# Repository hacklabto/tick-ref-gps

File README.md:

tick-ref-gps
============

GPS reference clock module for tick.hacklab.to. Part of tick-ref chassis.

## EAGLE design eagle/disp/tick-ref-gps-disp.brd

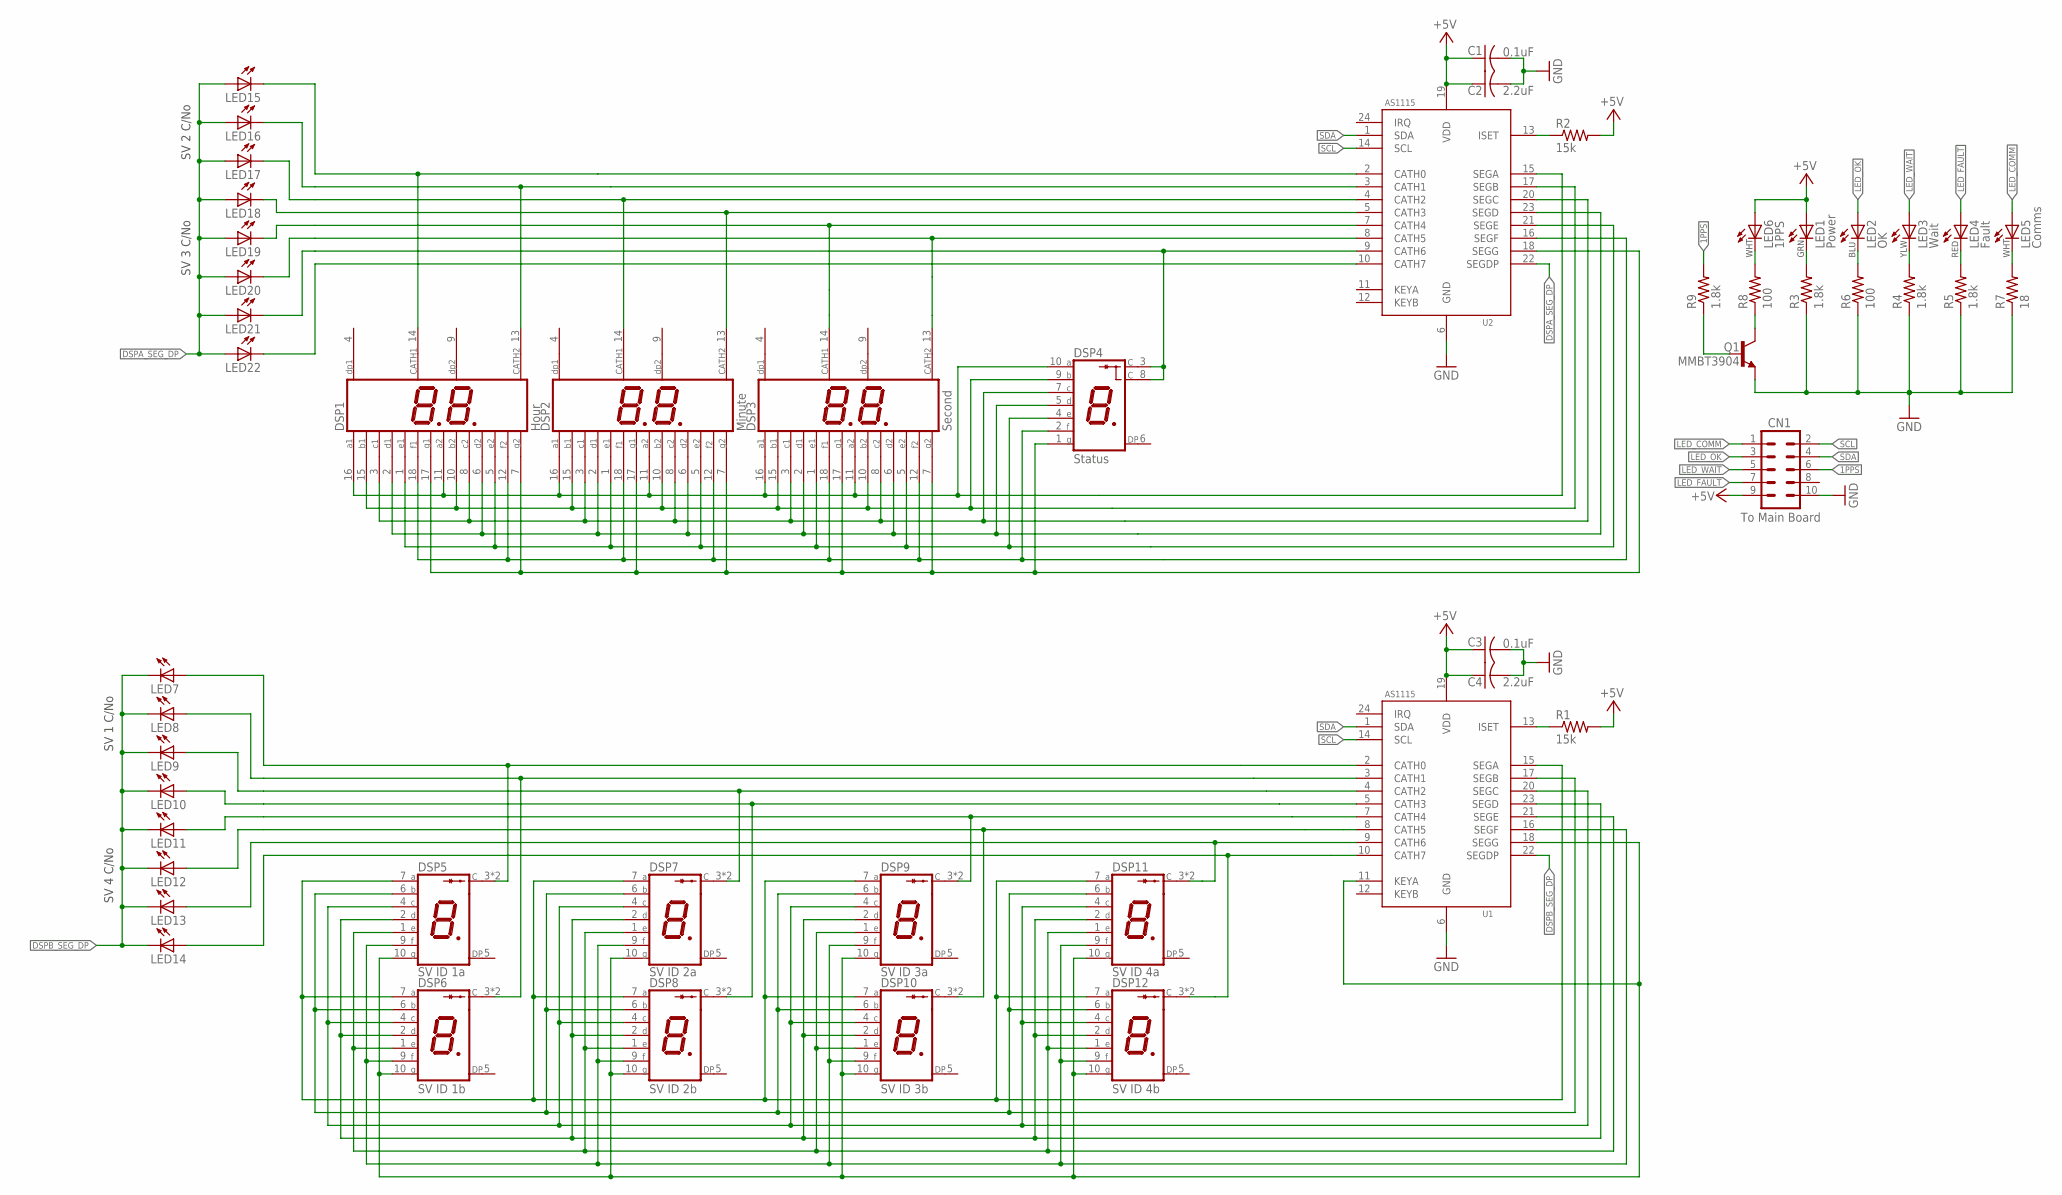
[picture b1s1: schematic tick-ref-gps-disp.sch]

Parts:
C1, C3: 0.1uF; C0603
C2, C4: 2.2uF; C0805
CN1: To Main Board; AVR_ICSP
DSP1: Hour; LUMEX-LDD-C81XRI
DSP2: Minute; LUMEX-LDD-C81XRI
DSP3: Second; LUMEX-LDD-C81XRI
DSP4: Status; S4301B
DSP5: SV ID 1a; KINGBRIGHT-ACSA02
DSP6: SV ID 1b; KINGBRIGHT-ACSA02
DSP7: SV ID 2a; KINGBRIGHT-ACSA02
DSP8: SV ID 2b; KINGBRIGHT-ACSA02
DSP9: SV ID 3a; KINGBRIGHT-ACSA02
DSP10: SV ID 3b; KINGBRIGHT-ACSA02
DSP11: SV ID 4a; KINGBRIGHT-ACSA02
DSP12: SV ID 4b; KINGBRIGHT-ACSA02
LED1: Power; LED5MM
LED2: OK; LED5MM
LED3: Wait; LED5MM
LED4: Fault; LED5MM
LED5: Comms; LED5MM
LED6: 1PPS; LED5MM
LED7, LED8, LED9, LED10, LED11, LED12, LED13, LED14, LED15, LED16, LED17, LED18, LED19, LED20, LED21, LED22: LEDCHIP-LED0805; CHIP-LED0805
Q1: MMBT3904; SOT23
R1, R2: 15k; R0603
R3, R4, R5, R9: 1.8k; R0603
R6, R8: 100; R0603
R7: 18; R0603
U1, U2: AS1115; QSOP24

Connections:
1PPS: CN1.6, R9.2
1PPS_Q: Q1.1 (B), R9.1
1PPS_R_Q: Q1.3 (C), R8.1
+5V: C1.1, C2.1, C3.1, C4.1, CN1.9, LED1.A, LED6.A, R1.2, R2.2, U1.19 (VDD), U2.19 (VDD)
CATH_HOUR_LS: DSP1.13 (CATH2), LED16.C, U2.3 (CATH1)
CATH_HOUR_MS: DSP1.14 (CATH1), LED15.C, U2.2 (CATH0)
CATH_MIN_LS: DSP2.13 (CATH2), LED18.C, U2.5 (CATH3)
CATH_MIN_MS: DSP2.14 (CATH1), LED17.C, U2.4 (CATH2)
CATH_SEC_LS: DSP3.13 (CATH2), LED20.C, U2.8 (CATH5)
CATH_SEC_MS: DSP3.14 (CATH1), LED19.C, U2.7 (CATH4)
CATH_STATUS_MS: DSP4.3 (C), DSP4.8 (C), LED21.C, U2.9 (CATH6)
CATH_STRENGTH: LED22.C, U2.10 (CATH7)
DSP5-C: DSP5.3 (CATH), DSP5.8 (CATH), LED7.A, U1.2 (CATH0)
DSP6-C: DSP6.3 (CATH), DSP6.8 (CATH), LED8.A, U1.3 (CATH1)
DSP7-C: DSP7.3 (CATH), DSP7.8 (CATH), LED9.A, U1.4 (CATH2)
DSP8-C: DSP8.3 (CATH), DSP8.8 (CATH), LED10.A, U1.5 (CATH3)
DSP9-C: DSP9.3 (CATH), DSP9.8 (CATH), LED11.A, U1.7 (CATH4)
DSP10-C: DSP10.3 (CATH), DSP10.8 (CATH), LED12.A, U1.8 (CATH5)
DSP11-C: DSP11.3 (CATH), DSP11.8 (CATH), LED13.A, U1.9 (CATH6)
DSP12-C: DSP12.3 (CATH), DSP12.8 (CATH), LED14.A, U1.10 (CATH7)
DSPA_SEG_A: DSP1.11 (A2), DSP1.16 (A1), DSP2.11 (A2), DSP2.16 (A1), DSP3.11 (A2), DSP3.16 (A1), DSP4.10 (A), U2.15 (SEGA)
DSPA_SEG_B: DSP1.10 (B2), DSP1.15 (B1), DSP2.10 (B2), DSP2.15 (B1), DSP3.10 (B2), DSP3.15 (B1), DSP4.9 (B), U2.17 (SEGB)
DSPA_SEG_C: DSP1.3 (C1), DSP1.8 (C2), DSP2.3 (C1), DSP2.8 (C2), DSP3.3 (C1), DSP3.8 (C2), DSP4.7 (C), U2.20 (SEGC)
DSPA_SEG_D: DSP1.2 (D1), DSP1.6 (D2), DSP2.2 (D1), DSP2.6 (D2), DSP3.2 (D1), DSP3.6 (D2), DSP4.5 (D), U2.23 (SEGD)
DSPA_SEG_DP: LED15.A, LED16.A, LED17.A, LED18.A, LED19.A, LED20.A, LED21.A, LED22.A, U2.22 (SEGDP)
DSPA_SEG_E: DSP1.1 (E1), DSP1.5 (E2), DSP2.1 (E1), DSP2.5 (E2), DSP3.1 (E1), DSP3.5 (E2), DSP4.4 (E), U2.21 (SEGE)
DSPA_SEG_F: DSP1.12 (F2), DSP1.18 (F1), DSP2.12 (F2), DSP2.18 (F1), DSP3.12 (F2), DSP3.18 (F1), DSP4.2 (F), U2.16 (SEGF)
DSPA_SEG_G: DSP1.7 (G2), DSP1.17 (G1), DSP2.7 (G2), DSP2.17 (G1), DSP3.7 (G2), DSP3.17 (G1), DSP4.1 (G), U2.18 (SEGG)
DSPB_SEG_A: DSP5.7 (A), DSP6.7 (A), DSP7.7 (A), DSP8.7 (A), DSP9.7 (A), DSP10.7 (A), DSP11.7 (A), DSP12.7 (A), U1.15 (SEGA)
DSPB_SEG_B: DSP5.6 (B), DSP6.6 (B), DSP7.6 (B), DSP8.6 (B), DSP9.6 (B), DSP10.6 (B), DSP11.6 (B), DSP12.6 (B), U1.17 (SEGB)
DSPB_SEG_C: DSP5.4 (C), DSP6.4 (C), DSP7.4 (C), DSP8.4 (C), DSP9.4 (C), DSP10.4 (C), DSP11.4 (C), DSP12.4 (C), U1.20 (SEGC)
DSPB_SEG_D: DSP5.2 (D), DSP6.2 (D), DSP7.2 (D), DSP8.2 (D), DSP9.2 (D), DSP10.2 (D), DSP11.2 (D), DSP12.2 (D), U1.23 (SEGD)
DSPB_SEG_DP: LED7.C, LED8.C, LED9.C, LED10.C, LED11.C, LED12.C, LED13.C, LED14.C, U1.22 (SEGDP)
DSPB_SEG_E: DSP5.1 (E), DSP6.1 (E), DSP7.1 (E), DSP8.1 (E), DSP9.1 (E), DSP10.1 (E), DSP11.1 (E), DSP12.1 (E), U1.21 (SEGE)
DSPB_SEG_F: DSP5.9 (F), DSP6.9 (F), DSP7.9 (F), DSP8.9 (F), DSP9.9 (F), DSP10.9 (F), DSP11.9 (F), DSP12.9 (F), U1.16 (SEGF)
DSPB_SEG_G: DSP5.10 (G), DSP6.10 (G), DSP7.10 (G), DSP8.10 (G), DSP9.10 (G), DSP10.10 (G), DSP11.10 (G), DSP12.10 (G), U1.11 (KEYA), U1.18 (SEGG)
GND: C1.2, C2.2, C3.2, C4.2, CN1.10, Q1.2 (E), R3.1, R4.1, R5.1, R6.1, R7.1, U1.6 (GND), U2.6 (GND)
LED1_R: LED1.K (C), R3.2
LED2_R: LED2.K (C), R6.2
LED3_R: LED3.K (C), R4.2
LED4_R: LED4.K (C), R5.2
LED5_R: LED5.K (C), R7.2
LED6_R: LED6.K (C), R8.2
LED_COMM: CN1.1, LED5.A
LED_FAULT: CN1.7, LED4.A
LED_ISET: R2.1, U2.13 (ISET)
LED_ISET1: R1.1, U1.13 (ISET)
LED_OK: CN1.3, LED2.A
LED_WAIT: CN1.5, LED3.A
SCL: CN1.2, U1.14 (SCL), U2.14 (SCL)
SDA: CN1.4, U1.1 (SDA), U2.1 (SDA)

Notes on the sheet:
GRN
YLW
RED
WHT
BLU
SV 1 C/No
SV 4 C/No
SV 2 C/No
SV 3 C/No

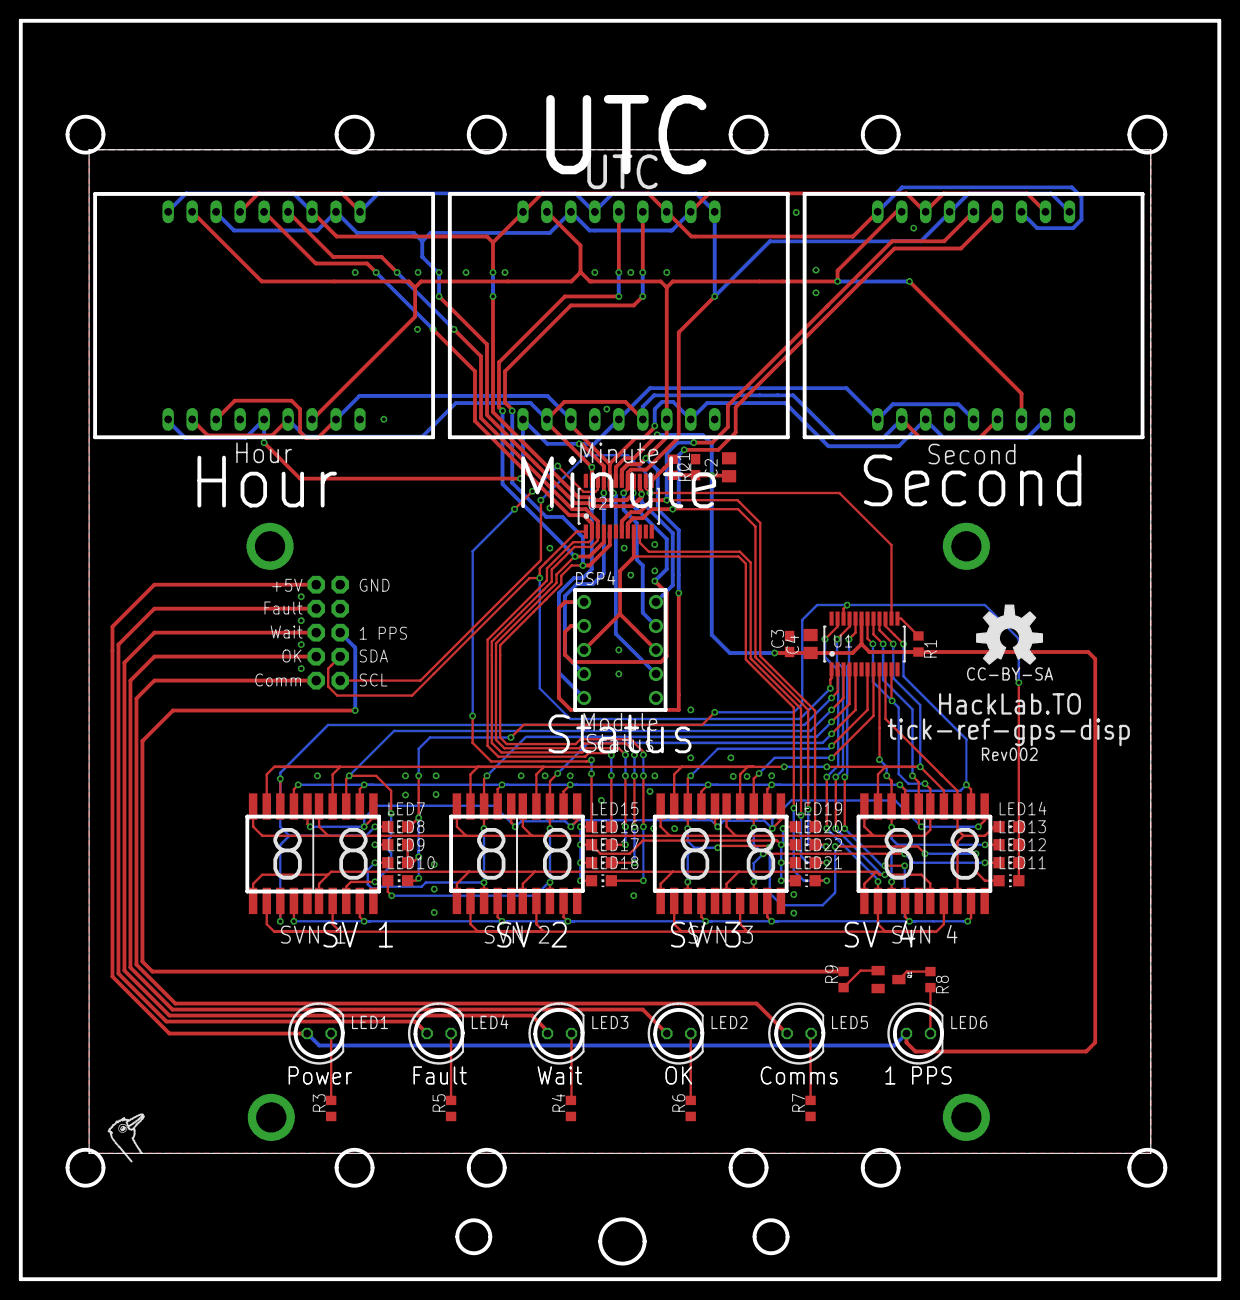
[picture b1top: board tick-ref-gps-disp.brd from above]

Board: 2 copper layers, 127.0 x 133.3 mm, 53 parts (1 on the bottom side), 51 nets.

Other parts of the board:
U$1: OSHW-LOGO-L
U$2: STRICH-LOGO-R

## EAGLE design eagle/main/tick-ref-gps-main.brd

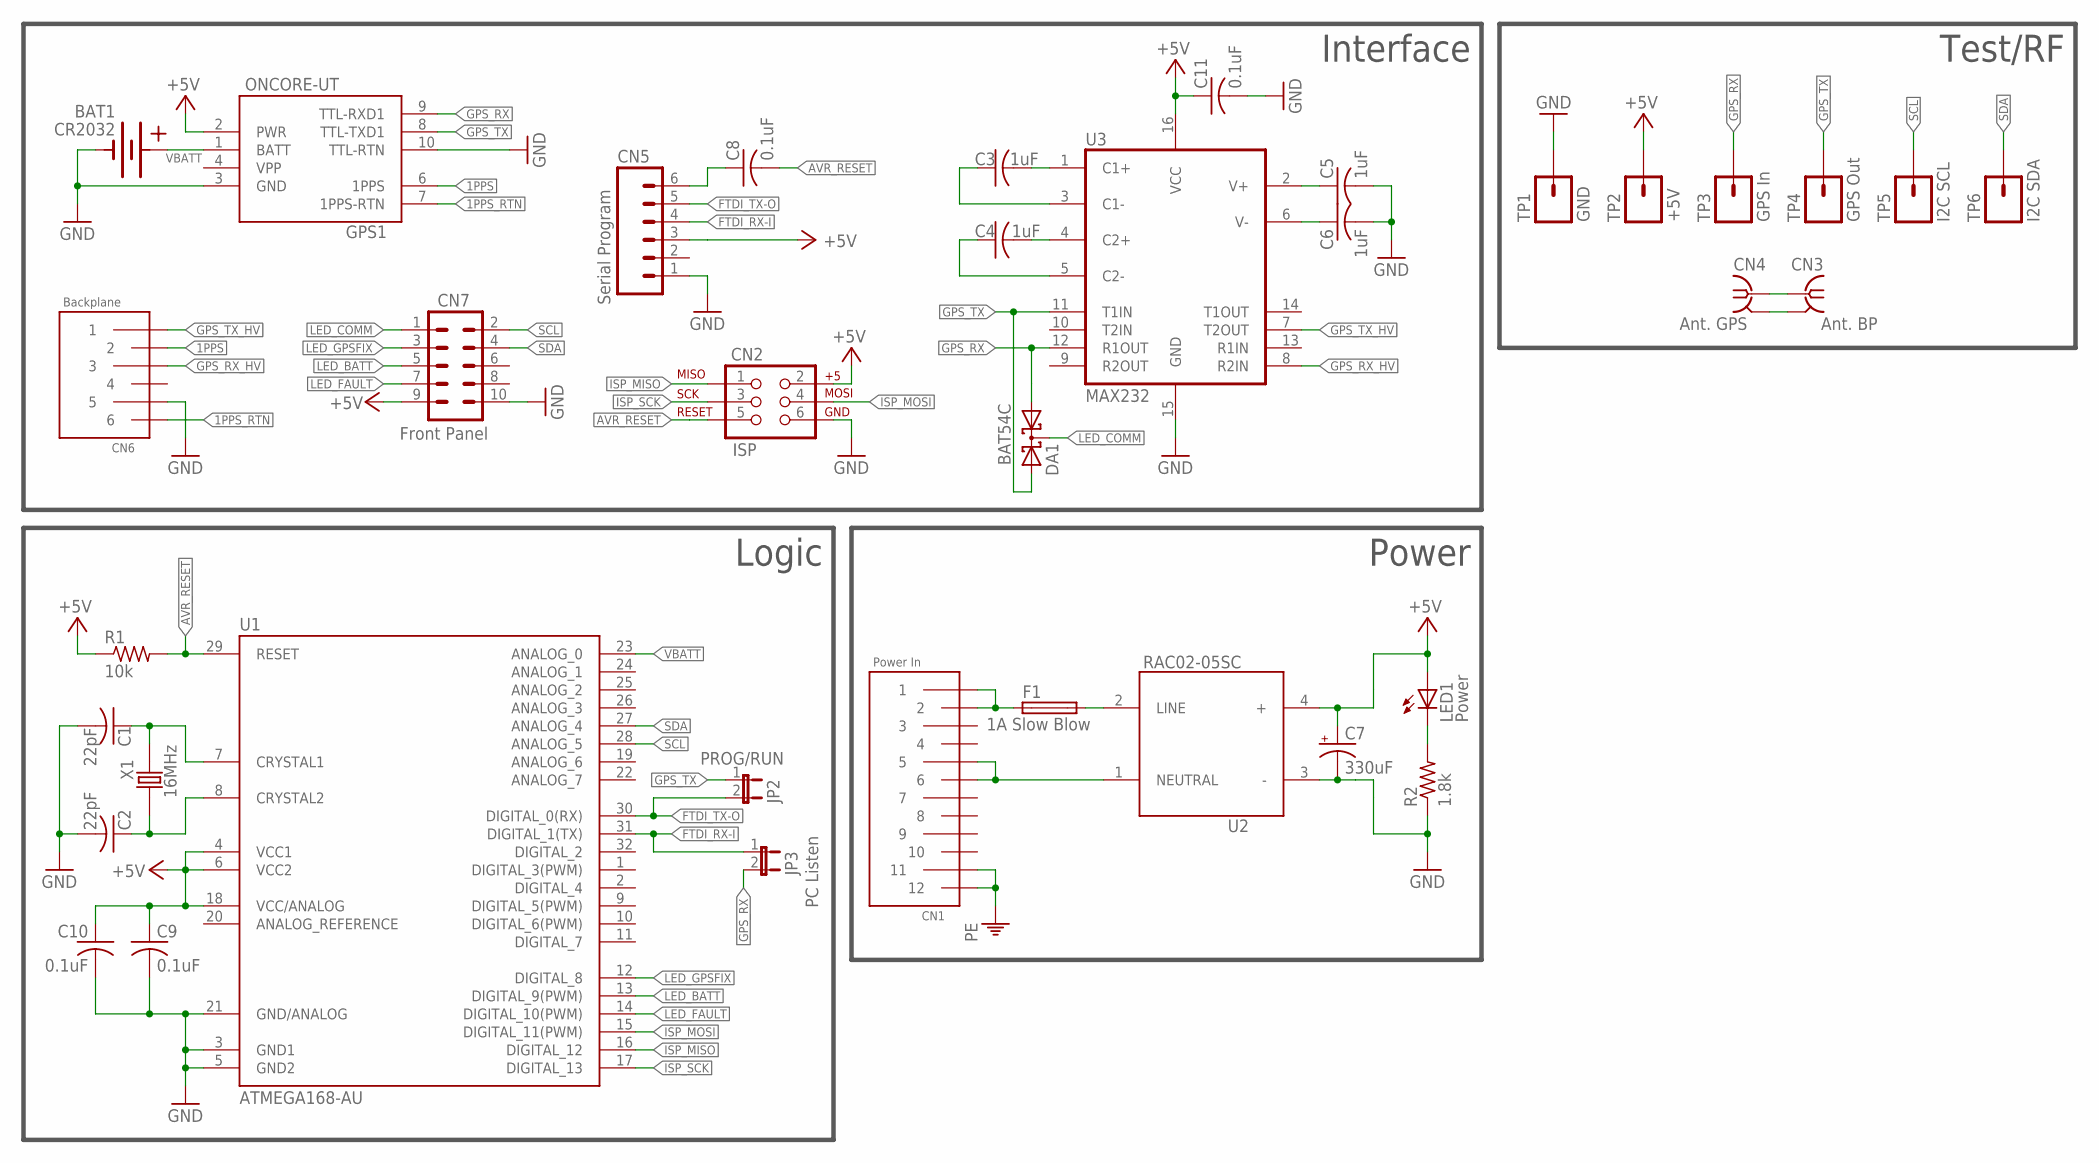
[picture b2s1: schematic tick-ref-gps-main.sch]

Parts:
BAT1: CR2032; BK-912-CR2032
C1, C2: 22pF; C0603
C3, C4, C5, C6: 1uF; C0603
C7: 330uF; E5-10,5
C8, C9, C10, C11: 0.1uF; C0603
CN1: Power In; EDGECON-M-0.15-12
CN2: ISP; 2X3_LOCK
CN3: Ant. BP; MMCX-J-P-X-ST-EM1-MKT
CN4: Ant. GPS; MOLEX-MCX-V
CN5: Serial Program; 1X06_LOCK
CN6: Backplane; EDGECON-M-0.1-6
CN7: Front Panel; AVR_ICSP
DA1: BAT54C; SOT23
F1: 1A Slow Blow; SH22,5A
GPS1: ONCORE-UT
JP2: PROG/RUN; 1X02_LOCK
JP3: PC Listen; SJ_2S-NO
LED1: Power; CHIP-LED0603
R1: 10k; R0603
R2: 1.8k; R0603
TP1: GND; 1X01
TP2: +5V; 1X01
TP3: GPS In; 1X01
TP4: GPS Out; 1X01
TP5: I2C SCL; 1X01
TP6: I2C SDA; 1X01
U1: ATMEGA168-AU; TQFP32-08
U2: RAC02-05SC; RAC0X-SC
U3: MAX232; SO016
X1: 16MHz; NX5032GA

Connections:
1PPS: CN6.2, GPS1.6 (1PPS)
1PPS_RTN: CN6.6, GPS1.7 (1PPS-RTN)
+5V: C7.+, C9.1, C10.1, C11.1, CN2.2, CN5.3, CN7.9, GPS1.2 (PWR), LED1.A, R1.1, TP2.1, U1.4 (VCC1), U1.6 (VCC2), U1.18 (VCC/ANALOG), U2.4 (+), U3.16 (VCC)
ANTENNA-GND: CN3.2@1 (GND), CN4.GND1 (GND), CN4.GND2 (GND), CN4.GND3 (GND), CN4.GND4 (GND)
ANTENNA-RF: CN3.1, CN4.CTR (A)
AVR_RESET: C8.2, CN2.5, R1.2, U1.29 (RESET)
FTDI_RTS: C8.1, CN5.6
FTDI_RX-I: CN5.4, JP3.1, U1.31 (DIGITAL_1(TX))
FTDI_TX-O: CN5.5, JP2.2, U1.30 (DIGITAL_0(RX))
GND: BAT1.- (-1), C1.2, C2.2, C5.2, C6.2, C7.-, C9.2, C10.2, C11.2, CN2.6, CN3.2@2 (GND), CN3.2@3 (GND), CN3.2@4 (GND), CN5.1, CN6.5, CN7.10, GPS1.3 (GND), GPS1.10 (TTL-RTN), R2.1, TP1.1, U1.3 (GND1), U1.5 (GND2), U1.21 (GND/ANALOG), U2.3 (-), U3.15 (GND)
GPS_RX: DA1.1 (A1), GPS1.9 (TTL-RXD1), JP3.2, TP3.1, U3.12 (R1OUT)
GPS_RX_HV: CN6.3, U3.8 (R2IN)
GPS_TX: DA1.2 (A2), GPS1.8 (TTL-TXD1), JP2.1, TP4.1, U3.11 (T1IN)
GPS_TX_HV: CN6.1, U3.7 (T2OUT)
ISP_MISO: CN2.1, U1.16 (DIGITAL_12)
ISP_MOSI: CN2.4, U1.15 (DIGITAL_11(PWM))
ISP_SCK: CN2.3, U1.17 (DIGITAL_13)
LED1_R: LED1.C, R2.2
LED_BATT: CN7.5, U1.13 (DIGITAL_9(PWM))
LED_COMM: CN7.1, DA1.3 (CC)
LED_FAULT: CN7.7, U1.14 (DIGITAL_10(PWM))
LED_GPSFIX: CN7.3, U1.12 (DIGITAL_8)
LINE: F1.2, U2.2 (LINE)
LINE-PREFUSE: CN1.1, CN1.2, F1.1
MAX232-C1+: C3.2, U3.1 (C1+)
MAX232-C1-: C3.1, U3.3 (C1-)
MAX232-C2+: C4.2, U3.4 (C2+)
MAX232-C2-: C4.1, U3.5 (C2-)
MAX232-V+: C5.1, U3.2 (V+)
MAX232-V-: C6.1, U3.6 (V-)
NEUTRAL: CN1.5, CN1.6, U2.1 (NEUTRAL)
PE: CN1.11, CN1.12
SCL: CN7.2, TP5.1, U1.28 (ANALOG_5)
SDA: CN7.4, TP6.1, U1.27 (ANALOG_4)
VBATT: BAT1.+1 (+2), GPS1.1 (BATT), U1.23 (ANALOG_0)
VPP: GPS1.4 (VPP)
XTAL1: C1.1, U1.7 (CRYSTAL1), X1.P$2 (2)
XTAL2: C2.1, U1.8 (CRYSTAL2), X1.P$1 (1)

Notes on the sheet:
Logic
Interface
Test/RF
Power

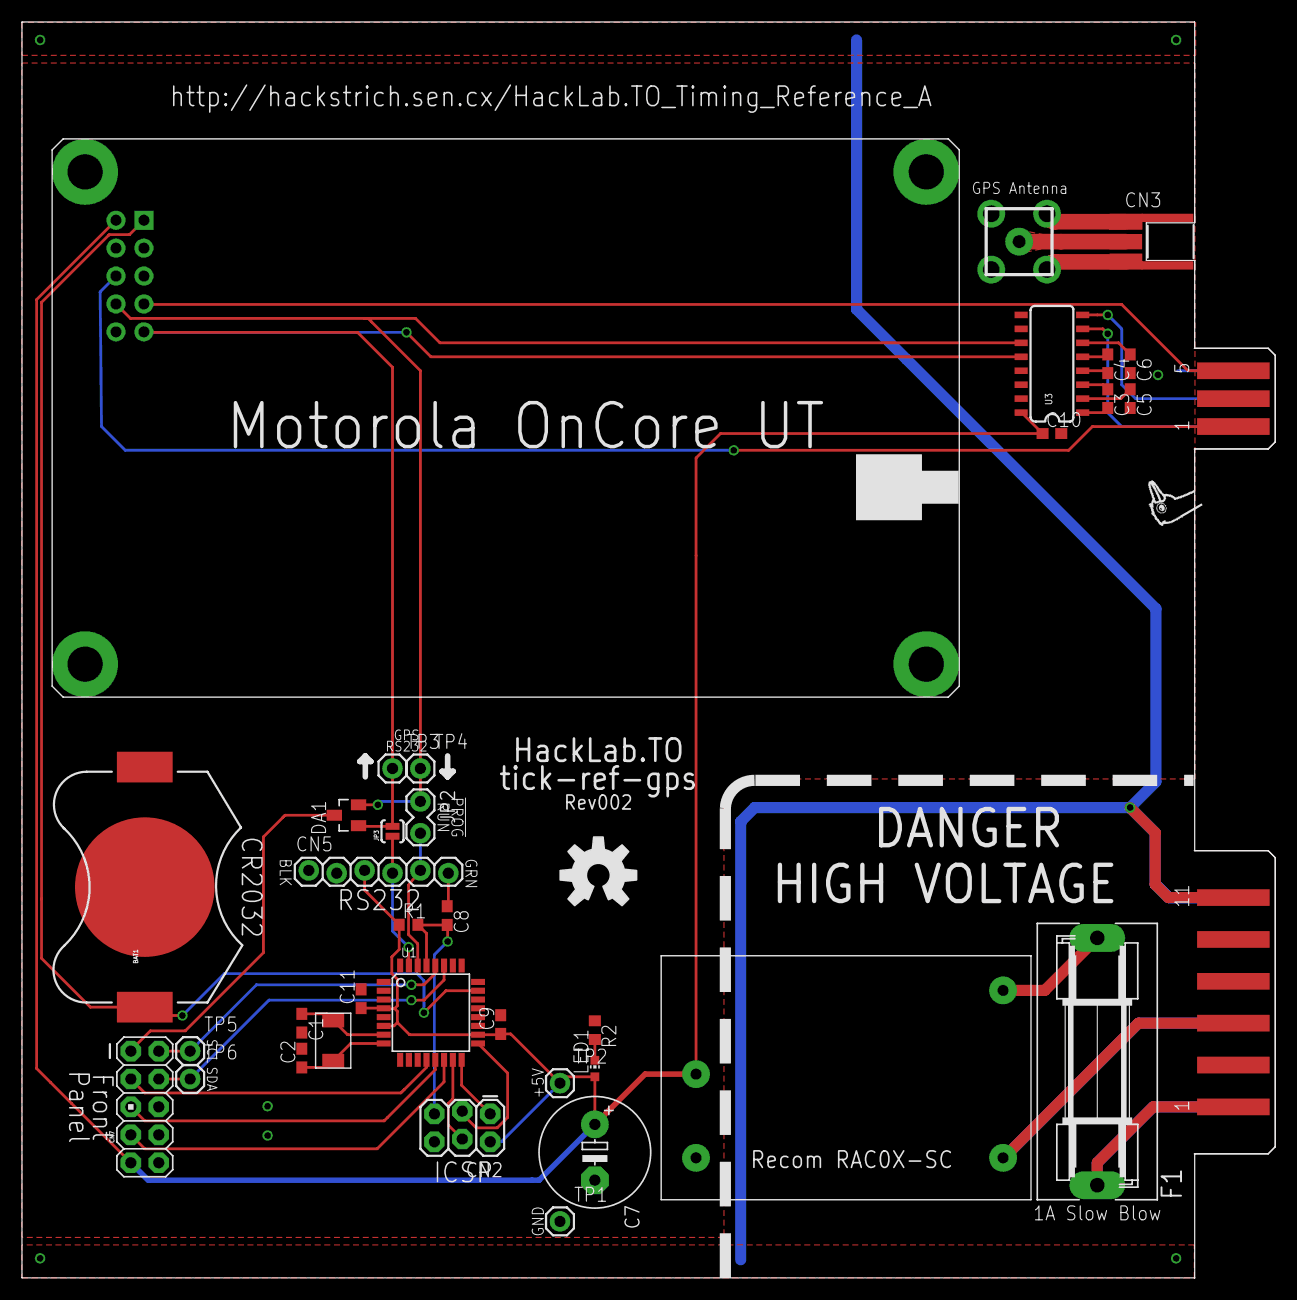
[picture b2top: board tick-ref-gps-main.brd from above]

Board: 2 copper layers, 114.0 x 114.3 mm, 39 parts (0 on the bottom side), 37 nets.

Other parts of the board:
U$1: OSHW-LOGO-L
U$2: STRICH-LOGO-R

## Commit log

2013-04-28 Adding completed/checklisted Rev001 schematic.
2013-04-28 Routing in progress, 42 airwires left to route.
2013-04-28 Completed routing, pending silk and checklist.
2013-04-28 Completed routing and silk, still needs final checklist run before CAMing.
2013-04-28 Adding BOM from Digi-Key.
2013-05-13 Reorganizing into main and display boards for new design. New main board schematicized and half routed.
2013-05-13 New main board design schematic done, half-routed.
2013-05-16 Finished routing board, need to run through checklist tomorrow before CAMing.
2013-05-16 Board checklist complete except for printing it out and comparing it to the existing modules connector-alignment-wise and size-wise.
2013-05-17 Display board schematic and layout electrically done, still need to figure out mechanical design and finalize this, plus run checklists.
2013-10-14 Fixed location of tStop/bStop strips for where PCB contacts the enclosure.
2013-10-14 Finished board outline.
2014-03-03 Schematic done for rev003 of the DISP board, 20 airwires left.
2014-03-08 Completed routing, checklist still needs to be run-through and silkscreen needs to be finished.
2014-03-08 Fixed off-center status display.
2014-03-08 Added milling layer for front panel cutting.
2014-03-09 Finally got around to measuring the actual enclosure, made the board the final width, switched to larger time displays, and rerouted for this. Still have to rearrange silk and make board slightly les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
2014-03-10 Milling layer for the prototype front panel added.
2014-03-20 Routing continues, 9 airwires to go.
2014-05-14 Completed routing tick-ref-gps-disp board rev002.
2014-05-14 CAM export for disp rev002!

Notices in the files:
eagle/disp/tick-ref-gps-disp.brd:
CC-BY-SA
parts and their libraries:
SparkFun-Connectors: Licensing: CC v3.0 Share-Alike You are welcome to use this library for commercial purposes.
